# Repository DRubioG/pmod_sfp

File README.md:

# pmod_sfp

This is the first attempt to design a PMOD board with an SFP connector

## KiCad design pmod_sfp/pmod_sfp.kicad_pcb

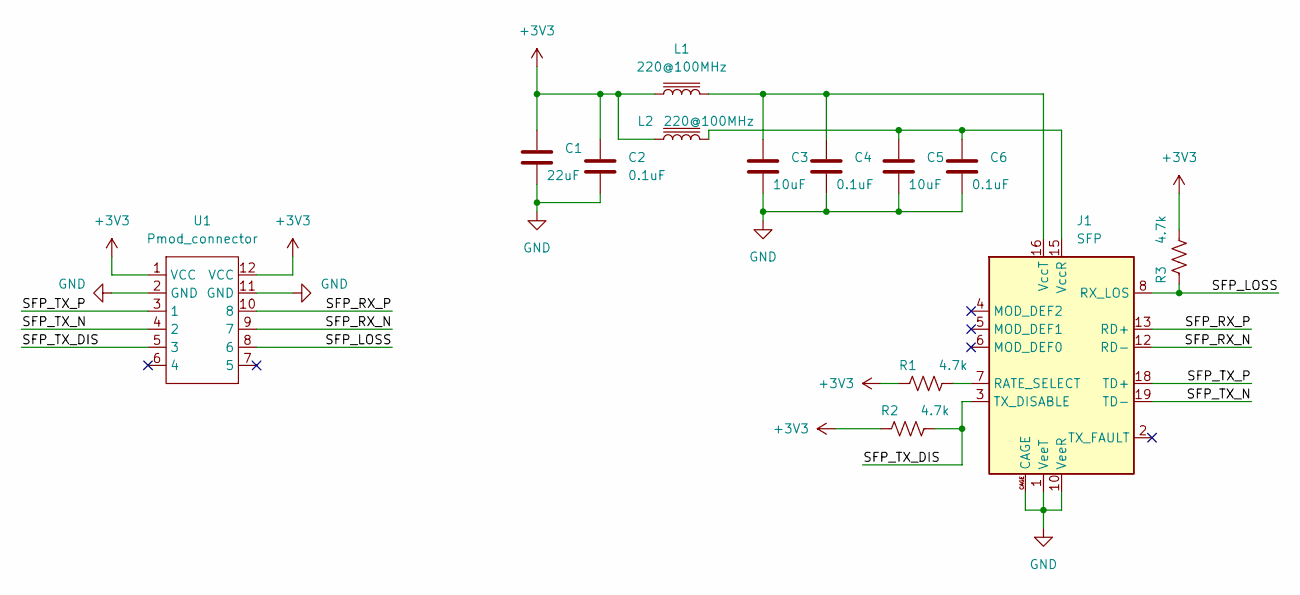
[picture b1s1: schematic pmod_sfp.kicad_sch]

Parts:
C1: 22uF; C_0402_1005Metric
C2, C4, C6: 0.1uF; C_0402_1005Metric
C3, C5: 10uF; C_0402_1005Metric
J1: SFP; Connector_SFP_and_Cage
L1, L2: 220@100MHz; L_0402_1005Metric
R1, R2, R3: 4.7k; R_0402_1005Metric
U1: Pmod_connector; PMOD_EXTENSION_BOARD

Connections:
+3V3: C1.1, C2.1, L1.1, L2.1, R1.1, R2.1, R3.2, U1.1 (VCC), U1.12 (VCC)
/SFP_LOSS: J1.8 (RX_LOS), R3.1, U1.8 (6)
/SFP_RX_N: J1.12 (RD-), U1.9 (7)
/SFP_RX_P: J1.13 (RD+), U1.10 (8)
/SFP_TX_DIS: J1.3 (TX_DISABLE), R2.2, U1.5 (3)
/SFP_TX_N: J1.19 (TD-), U1.4 (2)
/SFP_TX_P: J1.18 (TD+), U1.3 (1)
GND: C1.2, C2.2, C3.2, C4.2, C5.2, C6.2, J1.1 (VeeT), J1.9 (VeeR), J1.10 (VeeR), J1.11 (VeeR), J1.14 (VeeR), J1.17 (VeeT), J1.20 (VeeT), J1.CAGE, U1.2 (GND), U1.11 (GND)
unnamed: C3.1, C4.1, J1.16 (VccT), L1.2
unnamed: C5.1, C6.1, J1.15 (VccR), L2.2
unnamed: J1.7 (RATE_SELECT), R1.2

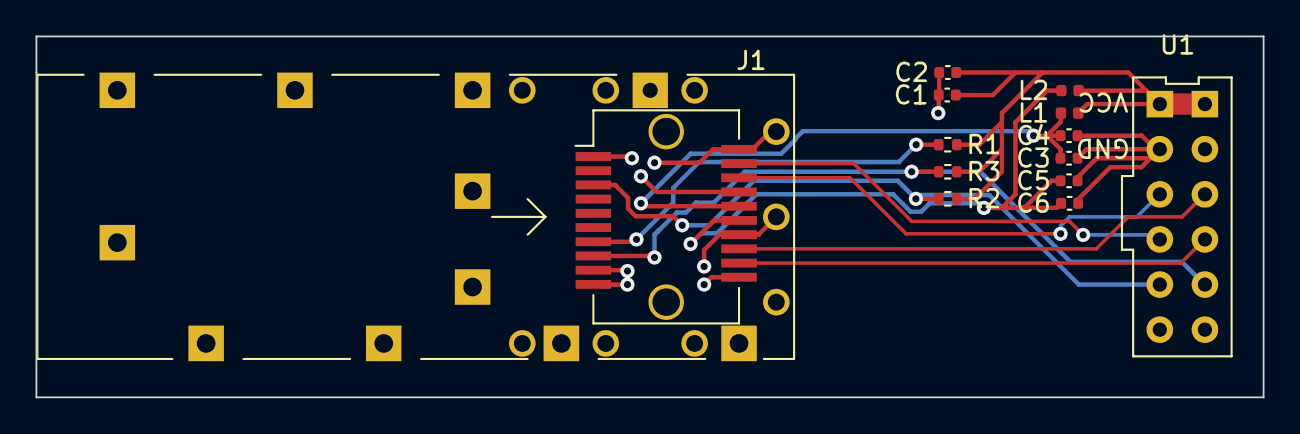
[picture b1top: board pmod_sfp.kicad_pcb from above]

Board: 2 copper layers, 69.1 x 20.3 mm, 13 parts (0 on the bottom side), 11 nets.

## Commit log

2023-02-12 Almost ended board
2023-07-28 first commint
    Board IMU done
